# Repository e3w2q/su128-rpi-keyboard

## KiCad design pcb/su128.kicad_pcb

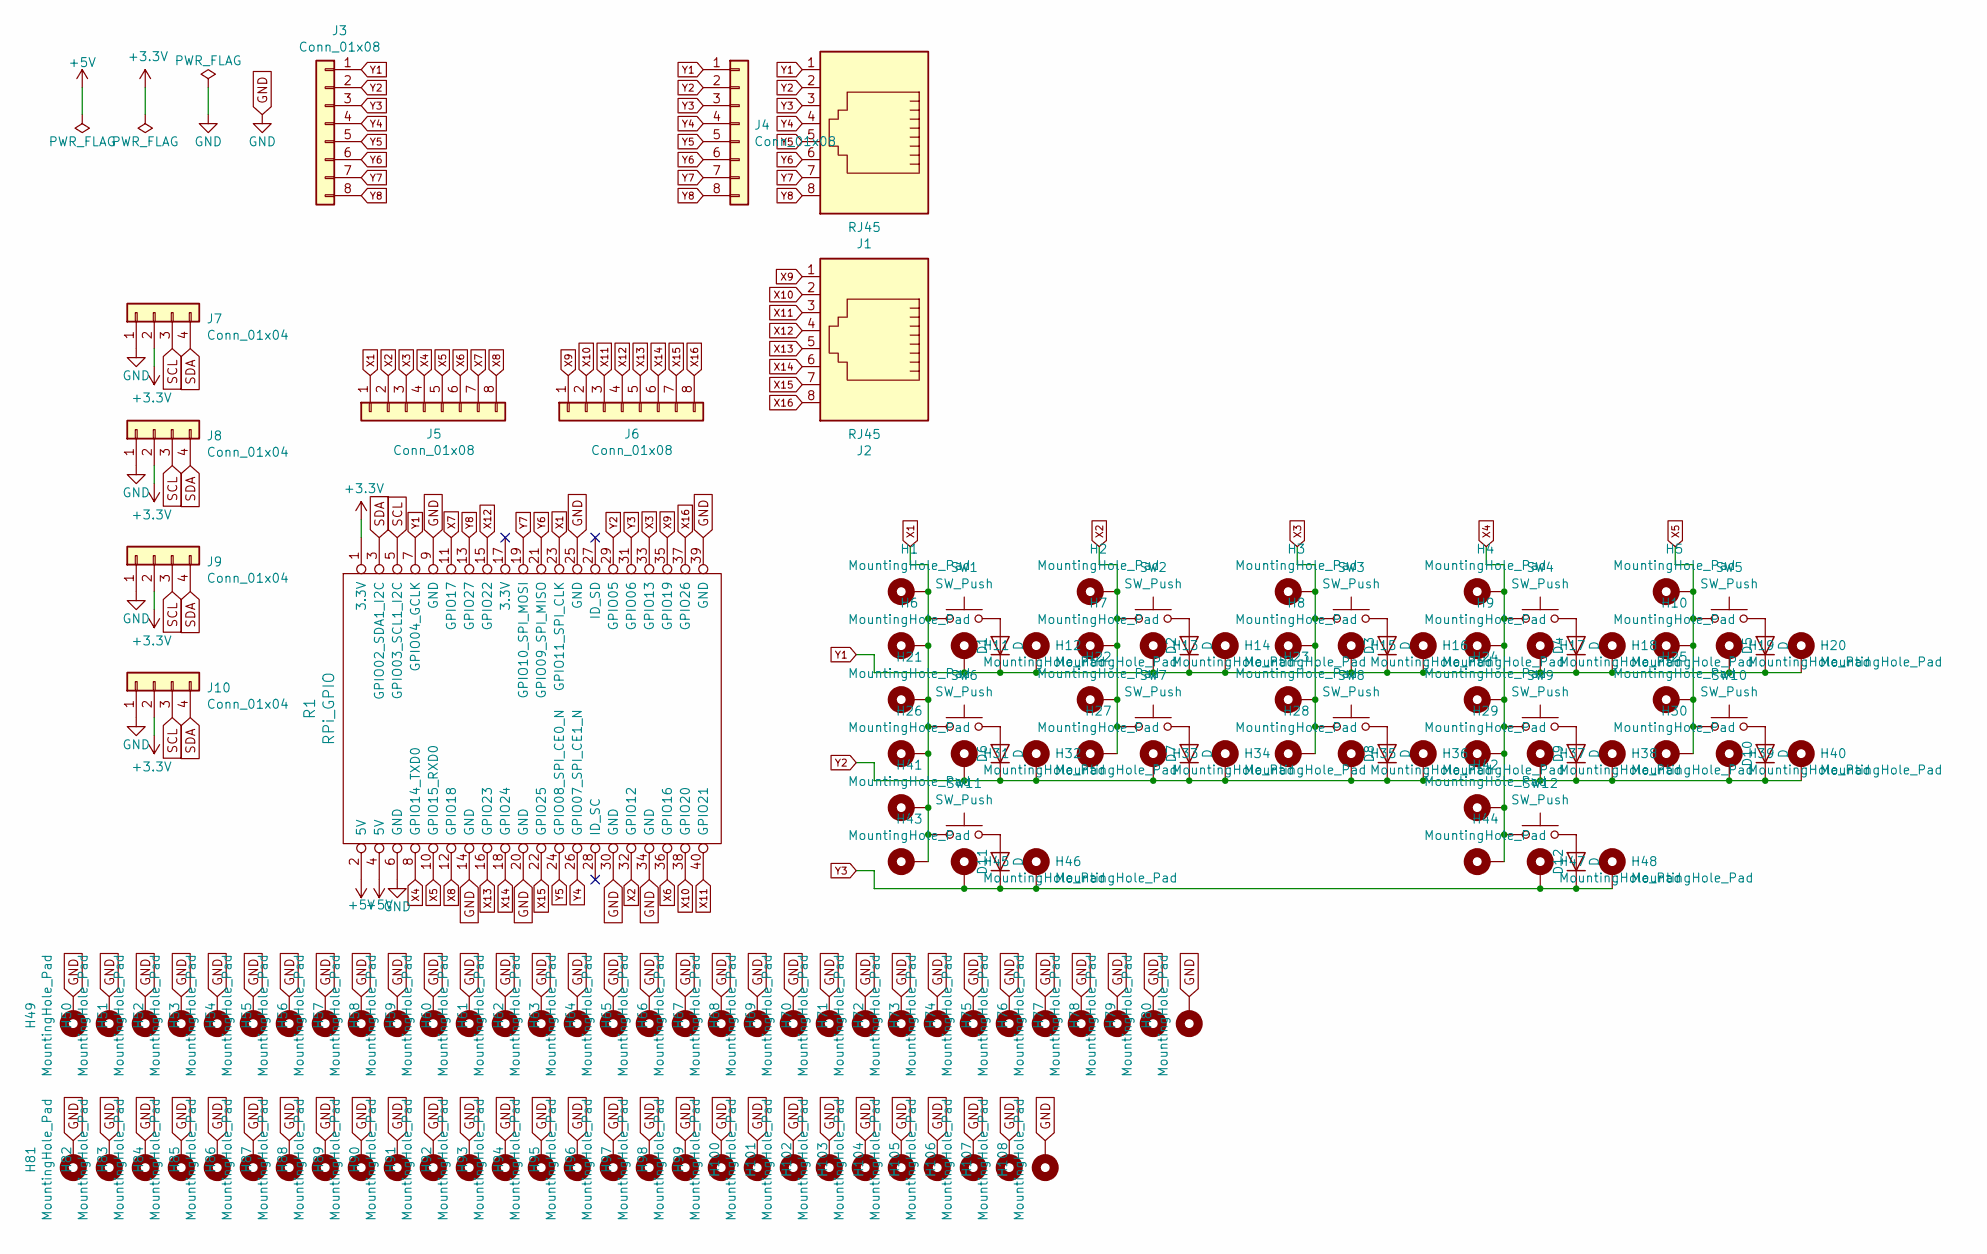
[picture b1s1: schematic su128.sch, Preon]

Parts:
D1, D2, D3, D4, D5, D6, D7, D8, D9, D10, D11, D12: D; diode
H1, H2, H3, H4, H5, H6, H7, H8, H9, H10, H11, H12, H13, H14, H15, H16, H17, H18, H19, H20, H21, H22, H23, H24, H25, H26, H27, H28, H29, H30, H31, H32, H33, H34, H35, H36, H37, H38, H39, H40, H41, H42, H43, H44, H45, H46, H47, H48: MountingHole_Pad; 1pin_conn
H49, H50, H51, H52, H53, H54, H55, H56, H57, H58, H59, H60, H61, H62, H63, H64, H65, H66, H67, H68, H69, H70, H71, H72, H73, H74, H75, H76, H77, H78, H79, H80, H81, H82, H83, H84, H85, H86, H87, H88, H89, H90, H91, H92, H93, H94, H95, H96, H97, H98, H99, H100, H101, H102, H103, H104, H105, H106, H107, H108: MountingHole_Pad; MountingHole_2.2mm_M2_Pad_Via
J1, J2: RJ45; RJ45_2
J3, J4, J5, J6: Conn_01x08; PinHeader_1x08_P2.54mm_Vertical_2Line
J7, J8, J9, J10: Conn_01x04; PinHeader_1x04_P2.54mm_Vertical
R1: RPi_GPIO; RPi_Pin_Header_Straight_2x20
SW1, SW2, SW3, SW4, SW5, SW6, SW7, SW8, SW9, SW10: SW_Push; CherryMX_MidHeight_Choc_Hotswap
SW11: SW_Push; CherryMX_MidHeight_Choc_Hotswap_2.25U
SW12: SW_Push; CherryMX_MidHeight_Choc_Hotswap_2.75U

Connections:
+3V3: J7.2, J8.2, J9.2, J10.2, R1.1 (3.3V)
GND: H49.1, H50.1, H51.1, H52.1, H53.1, H54.1, H55.1, H56.1, H57.1, H58.1, H59.1, H60.1, H61.1, H62.1, H63.1, H64.1, H65.1, H66.1, H67.1, H68.1, H69.1, H70.1, H71.1, H72.1, H73.1, H74.1, H75.1, H76.1, H77.1, H78.1, H79.1, H80.1, H81.1, H82.1, H83.1, H84.1, H85.1, H86.1, H87.1, H88.1, H89.1, H90.1, H91.1, H92.1, H93.1, H94.1, H95.1, H96.1, H97.1, H98.1, H99.1, H100.1, H101.1, H102.1, H103.1, H104.1, H105.1, H106.1, H107.1, H108.1, J7.1, J8.1, J9.1, J10.1, R1.6 (GND), R1.9 (GND), R1.14 (GND), R1.20 (GND), R1.25 (GND), R1.30 (GND), R1.34 (GND), R1.39 (GND)
unnamed: D1.2 (A), SW1.2
unnamed: D2.2 (A), SW2.2
unnamed: D3.2 (A), SW3.2
unnamed: D4.2 (A), SW4.2
unnamed: D5.2 (A), SW5.2
unnamed: D6.2 (A), SW6.2
unnamed: D7.2 (A), SW7.2
unnamed: D8.2 (A), SW8.2
unnamed: D9.2 (A), SW9.2
unnamed: D10.2 (A), SW10.2
unnamed: D11.2 (A), SW11.2
unnamed: D12.2 (A), SW12.2
SCL: J7.3, J8.3, J9.3, J10.3, R1.5 (GPIO03_SCL1_I2C)
SDA: J7.4, J8.4, J9.4, J10.4, R1.3 (GPIO02_SDA1_I2C)
X1: H1.1, H6.1, H21.1, H26.1, H41.1, H43.1, J5.1, R1.23 (GPIO11_SPI_CLK), SW1.1, SW6.1, SW11.1
X2: H2.1, H7.1, H22.1, H27.1, J5.2, R1.32 (GPIO12), SW2.1, SW7.1
X3: H3.1, H8.1, H23.1, H28.1, J5.3, R1.33 (GPIO13), SW3.1, SW8.1
X4: H4.1, H9.1, H24.1, H29.1, H42.1, H44.1, J5.4, R1.8 (GPIO14_TXD0), SW4.1, SW9.1, SW12.1
X5: H5.1, H10.1, H25.1, H30.1, J5.5, R1.10 (GPIO15_RXD0), SW5.1, SW10.1
X6: J5.6, R1.36 (GPIO16)
X7: J5.7, R1.11 (GPIO17)
X8: J5.8, R1.12 (GPIO18)
X9: J2.1, J6.1, R1.35 (GPIO19)
X10: J2.2, J6.2, R1.38 (GPIO20)
X11: J2.3, J6.3, R1.40 (GPIO21)
X12: J2.4, J6.4, R1.15 (GPIO22)
X13: J2.5, J6.5, R1.16 (GPIO23)
X14: J2.6, J6.6, R1.18 (GPIO24)
X15: J2.7, J6.7, R1.22 (GPIO25)
X16: J2.8, J6.8, R1.37 (GPIO26)
Y1: D1.1 (K), D2.1 (K), D3.1 (K), D4.1 (K), D5.1 (K), H11.1, H12.1, H13.1, H14.1, H15.1, H16.1, H17.1, H18.1, H19.1, H20.1, J1.1, J3.1, J4.1, R1.7 (GPIO04_GCLK)
Y2: D6.1 (K), D7.1 (K), D8.1 (K), D9.1 (K), D10.1 (K), H31.1, H32.1, H33.1, H34.1, H35.1, H36.1, H37.1, H38.1, H39.1, H40.1, J1.2, J3.2, J4.2, R1.29 (GPIO05)
Y3: D11.1 (K), D12.1 (K), H45.1, H46.1, H47.1, H48.1, J1.3, J3.3, J4.3, R1.31 (GPIO06)
Y4: J1.4, J3.4, J4.4, R1.26 (GPIO07_SPI_CE1_N)
Y5: J1.5, J3.5, J4.5, R1.24 (GPIO08_SPI_CE0_N)
Y6: J1.6, J3.6, J4.6, R1.21 (GPIO09_SPI_MISO)
Y7: J1.7, J3.7, J4.7, R1.19 (GPIO10_SPI_MOSI)
Y8: J1.8, J3.8, J4.8, R1.13 (GPIO27)

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
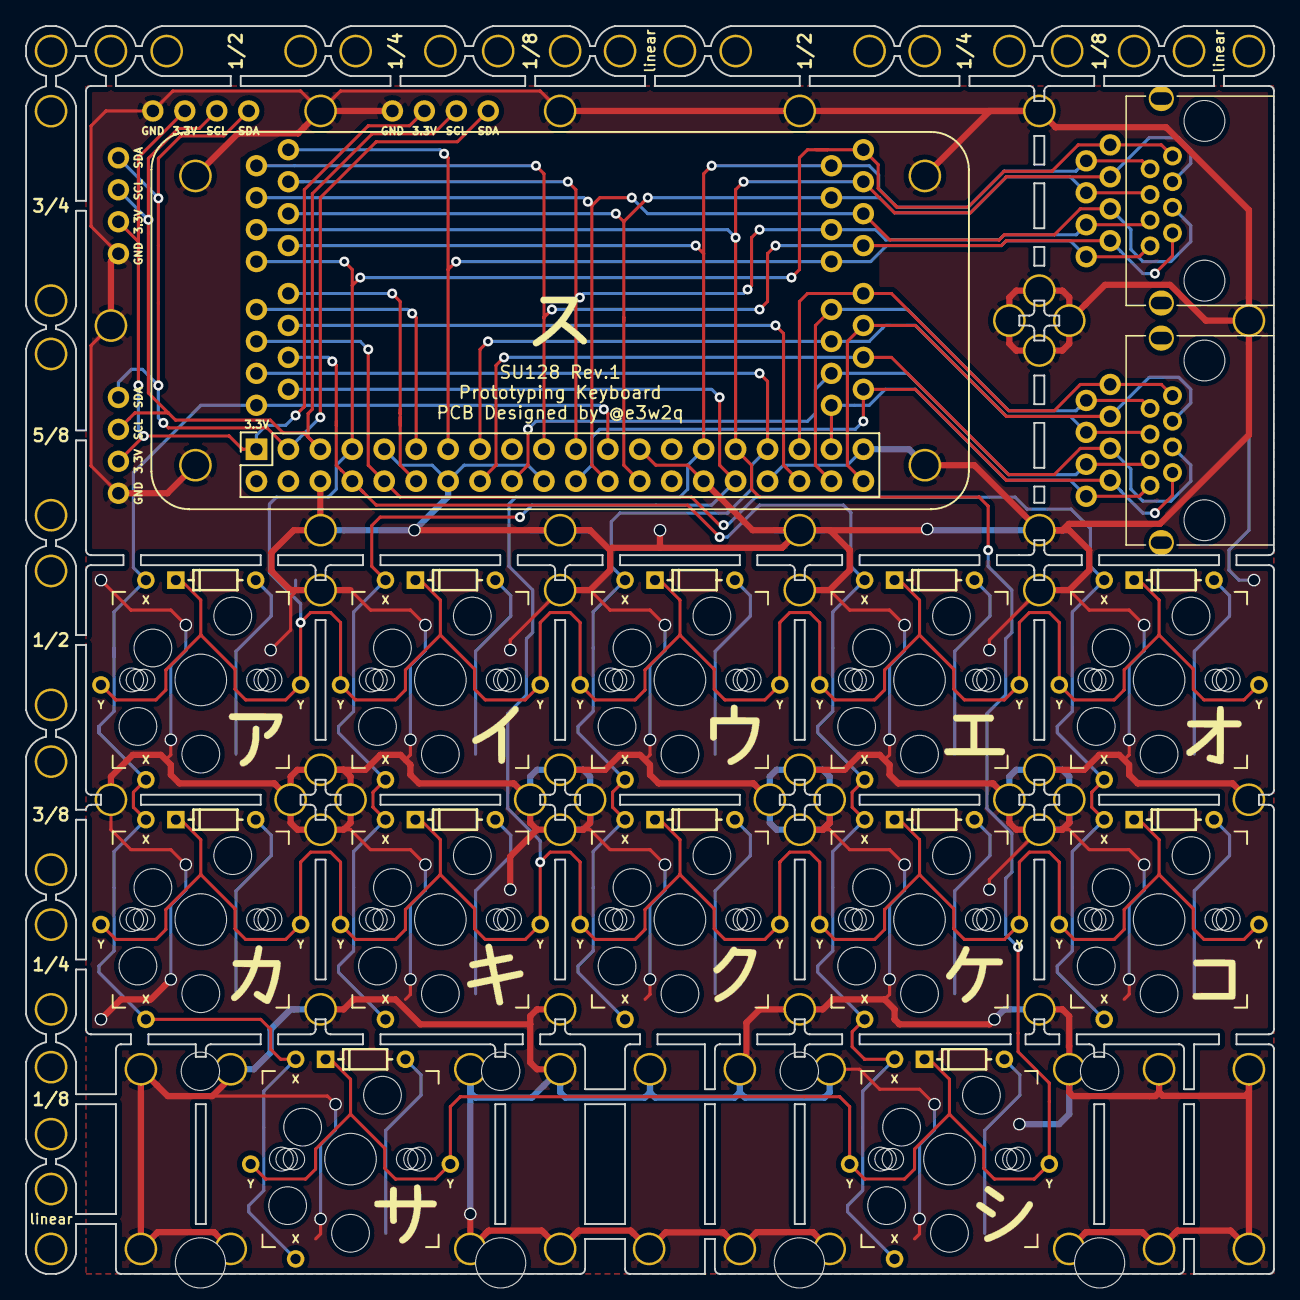
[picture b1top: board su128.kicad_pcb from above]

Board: 2 copper layers, 99.2 x 99.2 mm, 143 parts (0 on the bottom side), 40 nets.

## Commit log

2019-05-23 1st commit
